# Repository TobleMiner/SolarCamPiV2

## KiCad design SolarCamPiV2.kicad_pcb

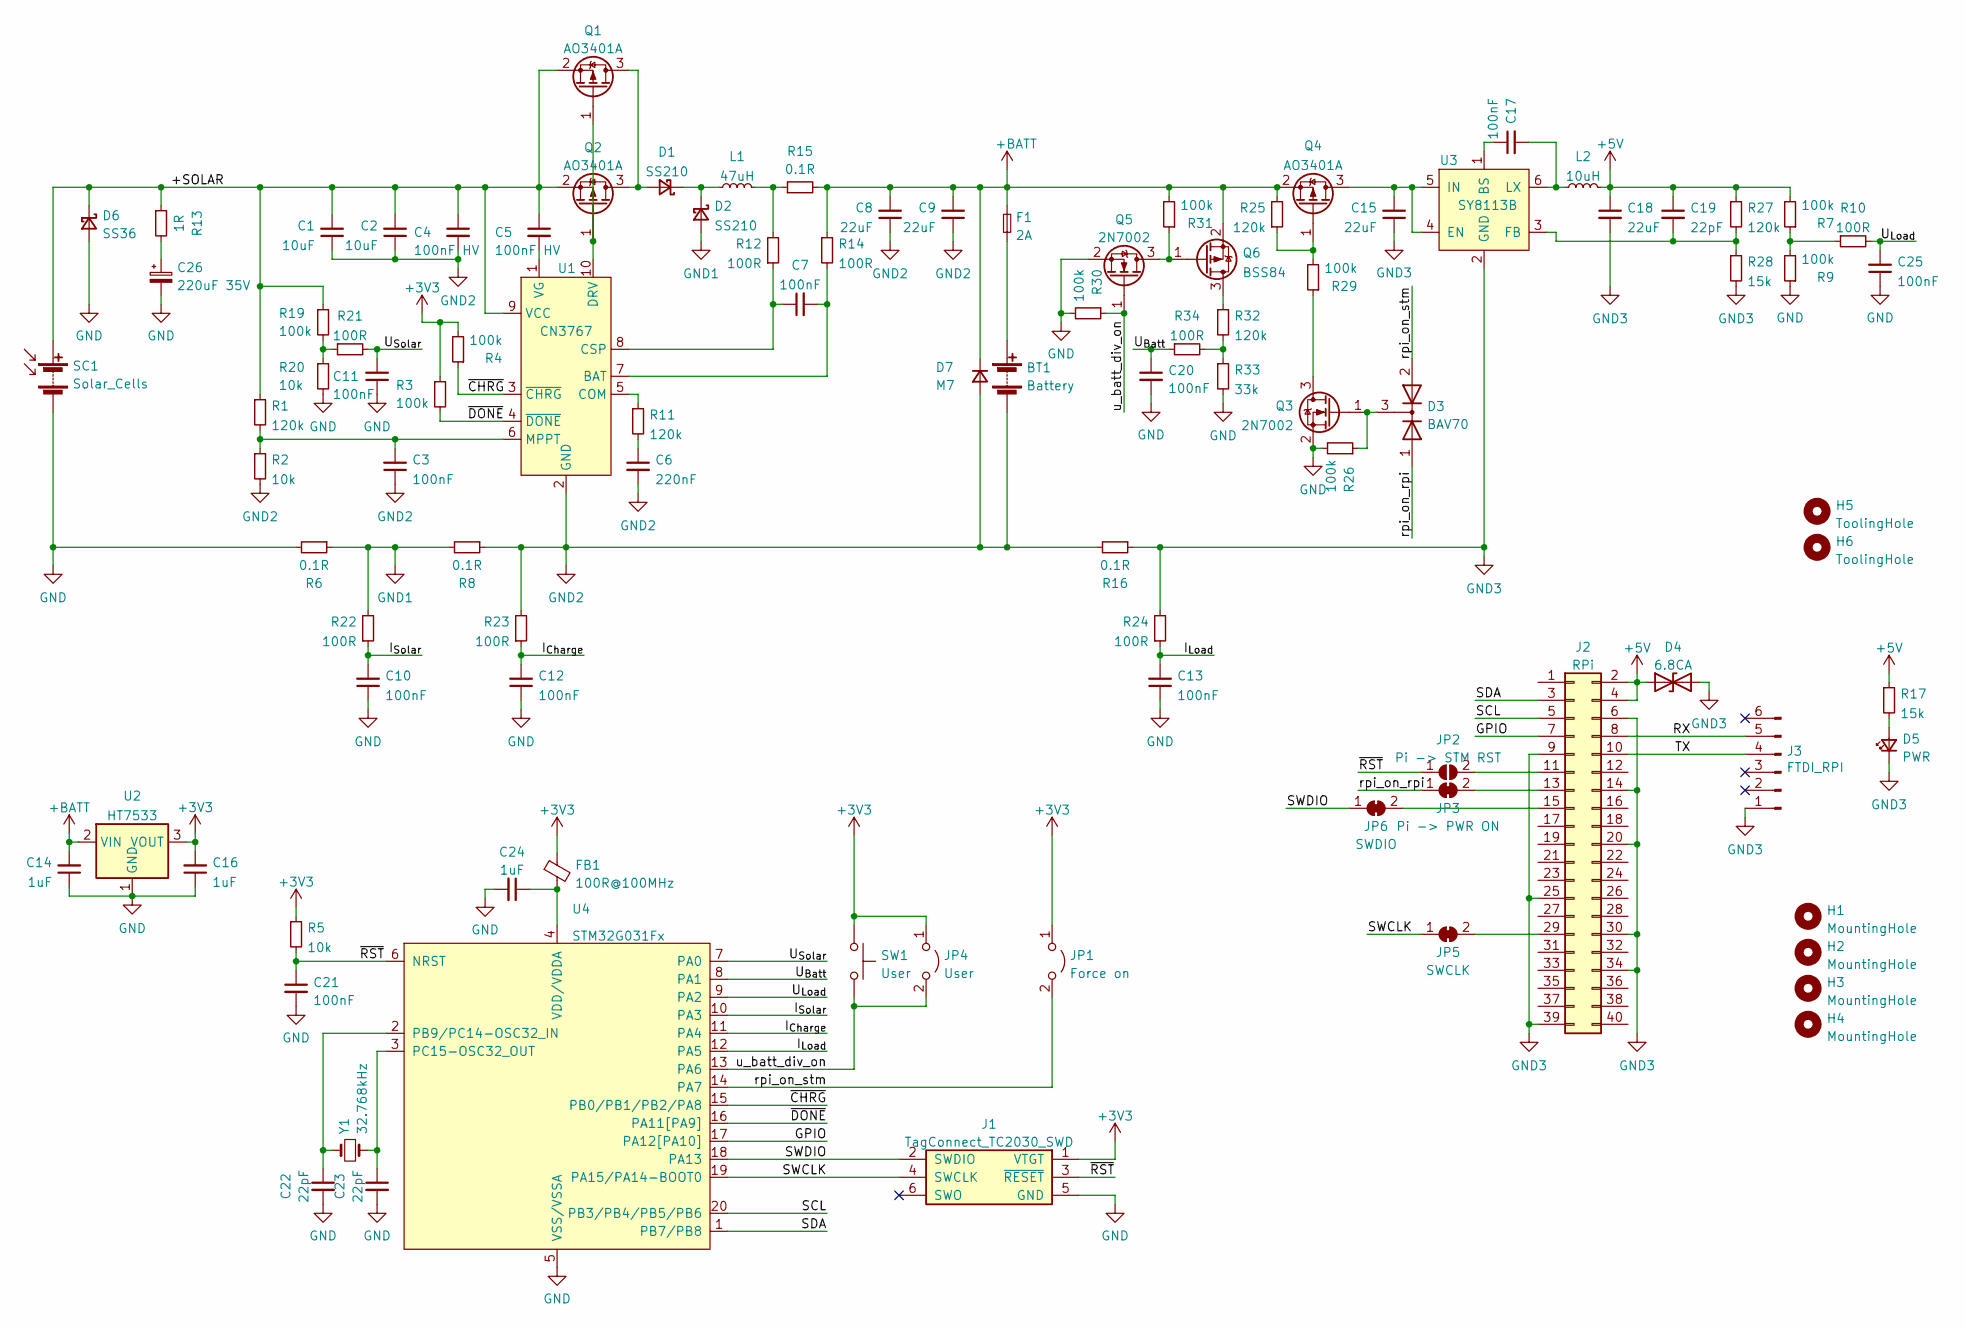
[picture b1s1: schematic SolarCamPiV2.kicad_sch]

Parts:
BT1: Battery; TerminalBlock_4Ucon_1x02_P3.50mm_Horizontal; LCSC C474892
C1, C2: 10uF; C_1206_3216Metric; LCSC C13585
C3, C7, C10, C11, C12, C13, C17, C20, C21, C25: 100nF; C_0402_1005Metric; LCSC C1525
C4, C5: 100nF HV; C_0603_1608Metric; LCSC C14663
C6: 220nF; C_0402_1005Metric; LCSC C16772
C8, C9, C15, C18: 22uF; C_0805_2012Metric; LCSC C45783
C14, C16, C24: 1uF; C_0402_1005Metric; LCSC C52923
C19, C22, C23: 22pF; C_0402_1005Metric; LCSC C1555
C26: 220uF 35V; CP_Elec_10x10; LCSC C134521
D1, D2: SS210; D_SMA; LCSC C14996
D3: BAV70; SOT-23
D4: 6.8CA; D_SMB; LCSC C78395
D5: PWR; LED_0603_1608Metric; LCSC C72043
D6: SS36; D_SMC; LCSC C35722
D7: M7; D_SMA; LCSC C95872
F1: 2A; Fuse_1206_3216Metric; LCSC C354895
FB1: 100R@100MHz; L_0805_2012Metric; LCSC C1017
H1, H2, H3, H4: MountingHole; MountingHole_2.7mm_M2.5
H5, H6: ToolingHole; ToolingHole_JLCSMT
J1: TagConnect_TC2030_SWD; Tag-Connect_TC2030-IDC-NL_2x03_P1.27mm_Vertical
J2: RPi; PinSocket_2x20_P2.54mm_Vertical
J3: FTDI_RPI; PinHeader_1x06_P2.54mm_Vertical
JP1: Force on; PinHeader_1x02_P2.54mm_Horizontal
JP2: Pi -> STM RST; SolderJumper-2_P1.3mm_Open_Pad1.0x1.5mm
JP3: Pi -> PWR ON; SolderJumper-2_P1.3mm_Bridged_Pad1.0x1.5mm
JP4: User; PinHeader_1x02_P2.54mm_Horizontal
JP5: SWCLK; SolderJumper-2_P1.3mm_Bridged_Pad1.0x1.5mm
JP6: SWDIO; SolderJumper-2_P1.3mm_Bridged_Pad1.0x1.5mm
L1: 47uH; L_Bourns_SRP7028A_7.3x6.6mm; LCSC C149588
L2: 10uH; L_Taiyo-Yuden_MD-4040; LCSC C340393
Q1, Q2, Q4: AO3401A; SOT-23; LCSC C15127
Q3, Q5: 2N7002; SOT-23; LCSC C8545
Q6: BSS84; SOT-23; LCSC C8492
R1, R11, R25, R27, R32: 120k; R_0402_1005Metric; LCSC C25750
R2, R5, R20: 10k; R_0402_1005Metric; LCSC C25744
R3, R4, R7, R9, R19, R26, R29, R30, R31: 100k; R_0402_1005Metric; LCSC C25741
R6, R8, R15, R16: 0.1R; R_1206_3216Metric; LCSC C25334
R10, R12, R14, R21, R22, R23, R24, R34: 100R; R_0402_1005Metric; LCSC C25076
R13: 1R; R_1206_3216Metric; LCSC C17928
R17, R28: 15k; R_0402_1005Metric; LCSC C25756
R33: 33k; R_0402_1005Metric; LCSC C25779
SC1: Solar_Cells; TerminalBlock_4Ucon_1x02_P3.50mm_Horizontal; LCSC C474892
SW1: User; SW_Push_SPST_NO_Alps_SKRK; LCSC C115357
U1: CN3767; SSOP-10_3.9x4.9mm_P1.00mm; LCSC C81968
U2: HT7533; SOT-89-3; LCSC C14289
U3: SY8113B; SOT-23-6; LCSC C78989
U4: STM32G031Fx; TSSOP-20_4.4x6.5mm_P0.65mm; LCSC C724040
Y1: 32.768kHz; Crystal_SMD_3215-2Pin_3.2x1.5mm; LCSC C32346

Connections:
+3V3: C16.2, FB1.1, J1.1 (VTGT), JP1.1 (A), JP4.1 (A), R3.1, R4.2, R5.1, SW1.1, U2.3 (VOUT)
+5V: C18.1, C19.1, D4.1 (A1), J2.2, J2.4, L2.2, R7.2, R17.1, R27.1
+BATT: C8.2, C9.2, C14.2, D7.1 (K), F1.2, Q4.2 (S), Q6.2 (S), R14.1, R15.2, R25.2, R31.2, U2.2 (VIN)
/+SOLAR: C1.2, C2.2, C4.1, C5.1, D6.1 (K), Q1.2 (S), Q2.2 (S), R1.1, R13.1, R19.1, SC1.1 (+), U1.9 (VCC)
/GPIO: J2.7, U4.17 (PA12[PA10])
/I_{Charge}: C12.2, R23.1, U4.11 (PA4)
/I_{Load}: C13.2, R24.1, U4.12 (PA5)
/I_{Solar}: C10.2, R22.1, U4.10 (PA3)
/RX: J2.8, J3.5
/SCL: J2.5, U4.20 (PB3/PB4/PB5/PB6)
/SDA: J2.3, U4.1 (PB7/PB8)
/SWCLK: J1.4 (SWCLK), JP5.1 (A), U4.19 (PA15/PA14-BOOT0)
/SWDIO: J1.2 (SWDIO), JP6.1 (A), U4.18 (PA13)
/TX: J2.10, J3.4
/U_{Batt}: C20.1, R34.1, U4.8 (PA1)
/U_{Load}: C25.2, R10.2, U4.9 (PA2)
/U_{Solar}: C11.2, R21.2, U4.7 (PA0)
/rpi_on_rpi: D3.1 (A), JP3.1 (A)
/rpi_on_stm: D3.2 (A), JP1.2 (B), U4.14 (PA7)
/u_batt_div_on: JP4.2 (B), Q5.1 (G), R30.1, SW1.2, U4.13 (PA6)
/~CHRG: R4.1, U1.3 (~CHRG), U4.15 (PB0/PB1/PB2/PA8)
/~DONE: R3.2, U1.4 (~DONE), U4.16 (PA11[PA9])
/~RST: C21.1, J1.3 (~RESET), JP2.1 (A), R5.2, U4.6 (NRST)
GND: C10.1, C11.1, C12.1, C13.1, C14.1, C16.1, C20.2, C21.2, C22.2, C23.2, C24.2, C25.1, C26.2, D6.2 (A), J1.5 (GND), Q3.2 (S), Q5.2 (S), R6.2, R9.1, R20.2, R26.2, R30.2, R33.2, SC1.2 (-), U2.1 (GND), U4.5 (VSS/VSSA)
GND1: D2.2 (A), R6.1, R8.2, R22.2
GND2: BT1.2 (-), C1.1, C2.1, C3.1, C4.2, C6.2, C8.1, C9.1, D7.2 (A), R2.2, R8.1, R16.2, R23.2, U1.2 (GND)
GND3: C15.1, C18.2, D4.2 (A2), D5.1 (K), J2.6, J2.9, J2.14, J2.20, J2.25, J2.30, J2.34, J2.39, J3.1, R16.1, R24.2, R28.2, U3.2 (GND)
unnamed: BT1.1 (+), F1.1
unnamed: C3.2, R1.2, R2.1, U1.6 (MPPT)
unnamed: C5.2, U1.1 (VG)
unnamed: C6.1, R11.2
unnamed: C7.1, R12.1, U1.8 (CSP)
unnamed: C7.2, R14.2, U1.7 (BAT)
unnamed: C15.2, Q4.3 (D), U3.4 (EN), U3.5 (IN)
unnamed: C17.1, U3.1 (BS)
unnamed: C17.2, L2.1, U3.6 (LX)
unnamed: C19.2, R27.2, R28.1, U3.3 (FB)
unnamed: C22.1, U4.2 (PB9/PC14-OSC32_IN), Y1.2
unnamed: C23.1, U4.3 (PC15-OSC32_OUT), Y1.1
unnamed: C24.1, FB1.2, U4.4 (VDD/VDDA)
unnamed: C26.1, R13.2
unnamed: D1.1 (K), D2.1 (K), L1.1
unnamed: D1.2 (A), Q1.3 (D), Q2.3 (D)
unnamed: D3.3 (K), Q3.1 (G), R26.1
unnamed: D5.2 (A), R17.2
unnamed: J2.11, JP2.2 (B)
unnamed: J2.13, JP3.2 (B)
unnamed: J2.15, JP6.2 (B)
unnamed: J2.29, JP5.2 (B)
unnamed: L1.2, R12.2, R15.1
unnamed: Q1.1 (G), Q2.1 (G), U1.10 (DRV)
unnamed: Q3.3 (D), R29.1
unnamed: Q4.1 (G), R25.1, R29.2
unnamed: Q5.3 (D), Q6.1 (G), R31.1
unnamed: Q6.3 (D), R32.1
unnamed: R7.1, R9.2, R10.1
unnamed: R11.1, U1.5 (COM)
unnamed: R19.2, R20.1, R21.1
unnamed: R32.2, R33.1, R34.2

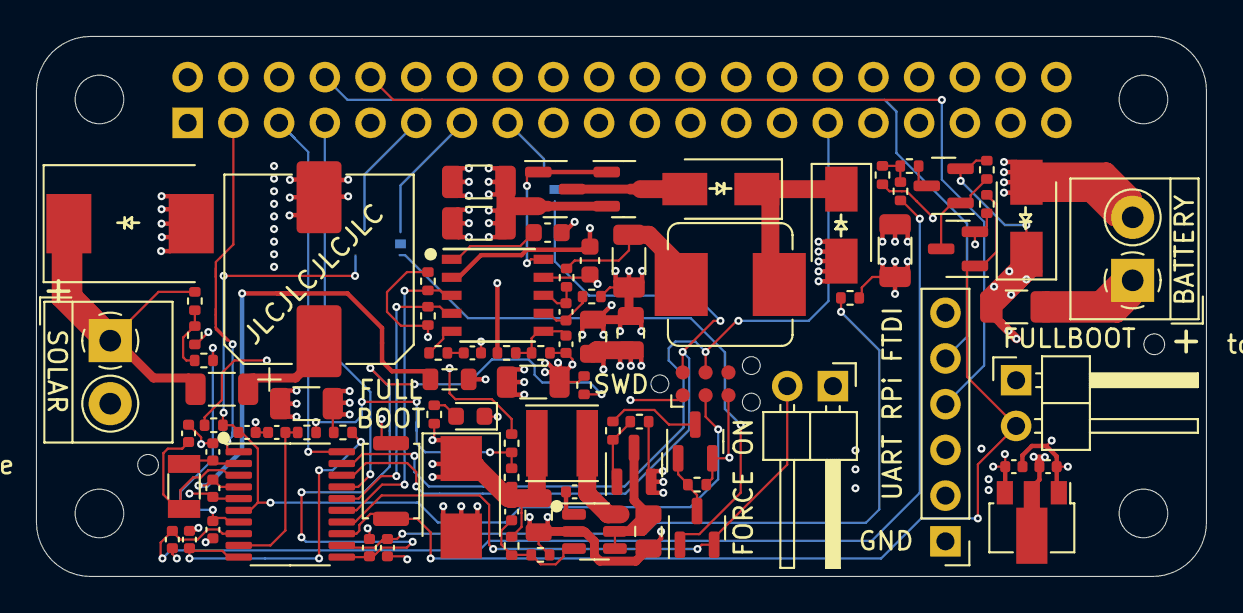
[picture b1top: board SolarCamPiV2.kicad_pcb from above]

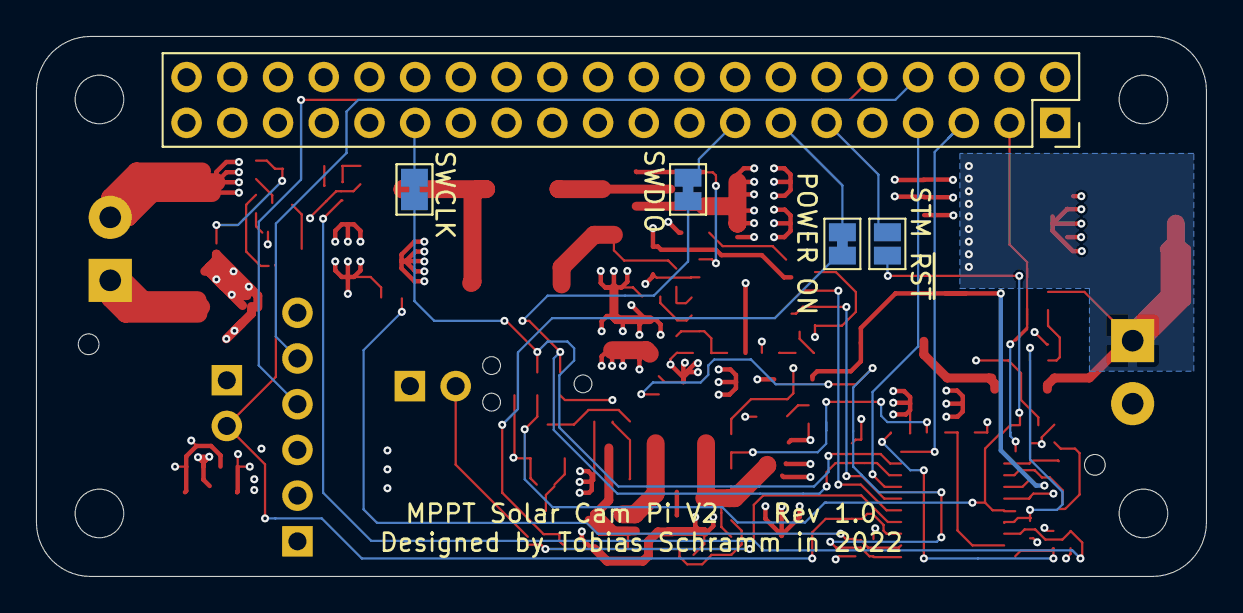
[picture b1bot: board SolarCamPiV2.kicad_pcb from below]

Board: 4 copper layers, 65.0 x 30.0 mm, 99 parts (5 on the bottom side), 59 nets.

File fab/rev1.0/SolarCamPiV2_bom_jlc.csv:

"Comment","Designator","Footprint","LCSC Part #"
"Battery","BT1","TerminalBlock_4Ucon_1x02_P3.50mm_Horizontal","C474892"
"10uF","C1,C2","C_1206_3216Metric","C13585"
"100nF","C3,C7,C10,C11,C12,C13,C17,C20,C21,C25","C_0402_1005Metric","C1525"
"100nF HV","C4,C5","C_0603_1608Metric","C14663"
"220nF","C6","C_0402_1005Metric","C16772"
"22uF","C8,C9,C15,C18","C_0805_2012Metric","C45783"
"1uF","C14,C16,C24","C_0402_1005Metric","C52923"
"22pF","C19,C22,C23","C_0402_1005Metric","C1555"
"220uF 35V","C26","CP_Elec_10x10","C134521"
"SS210","D1,D2","D_SMA","C14996"
"BAV70","D3","SOT-23","C68978"
"6.8CA","D4","D_SMB","C78395"
"PWR","D5","LED_0603_1608Metric","C72043"
"SS36","D6","D_SMC","C35722"
"M7","D7","D_SMA","C95872"
"2A","F1","Fuse_1206_3216Metric","C354895"
"100R@100MHz","FB1","L_0805_2012Metric","C1017"
"FTDI_RPI","J3","PinHeader_1x06_P2.54mm_Vertical","C2935912"
"Force on","JP1","PinHeader_1x02_P2.54mm_Horizontal","C2935927"
"User","JP4","PinHeader_1x02_P2.54mm_Horizontal","C2935927"
"47uH","L1","L_Bourns_SRP7028A_7.3x6.6mm","C149588"
"10uH","L2","L_Taiyo-Yuden_MD-4040","C340393"
"AO3401A","Q1,Q2,Q4","SOT-23","C15127"
"2N7002","Q3,Q5","SOT-23","C8545"
"BSS84","Q6","SOT-23","C8492"
"120k","R1,R11,R25,R27,R32","R_0402_1005Metric","C25750"
"10k","R2,R5,R20","R_0402_1005Metric","C25744"
"100k","R3,R4,R7,R9,R19,R26,R29,R30,R31","R_0402_1005Metric","C25741"
"0.1R","R6,R8,R15,R16","R_1206_3216Metric","C25334"
"100R","R10,R12,R14,R21,R22,R23,R24,R34","R_0402_1005Metric","C25076"
"1R","R13","R_1206_3216Metric","C17928"
"15k","R17,R28","R_0402_1005Metric","C25756"
"33k","R33","R_0402_1005Metric","C25779"
"Solar_Cells","SC1","TerminalBlock_4Ucon_1x02_P3.50mm_Horizontal","C474892"
"User","SW1","SW_Push_SPST_NO_Alps_SKRK","C115357"
"CN3767","U1","SSOP-10_3.9x4.9mm_P1.00mm","C81968"
"HT7533","U2","SOT-89-3","C14289"
"SY8113B","U3","SOT-23-6","C78989"
"STM32G031Fx","U4","TSSOP-20_4.4x6.5mm_P0.65mm","C724040"
"32.768kHz","Y1","Crystal_SMD_3215-2Pin_3.2x1.5mm","C32346"

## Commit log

2022-04-16 Add RPi socket
2022-04-16 Change MTTP charge current setpoint to 1.2A
2022-04-16 Add battery fuse
2022-04-16 Add reverse polarity protection
2022-04-16 Fix Q2 polarity
2022-04-18 Layout power conversion subcomponents
2022-05-29 Finish component placement
2022-05-29 Finish routing
2022-05-29 DFM, add pin 1 designators
2022-05-29 Connect SWD to RPi GPIOs
2022-05-29 Add 3d models
2022-05-29 Add fabrication files
